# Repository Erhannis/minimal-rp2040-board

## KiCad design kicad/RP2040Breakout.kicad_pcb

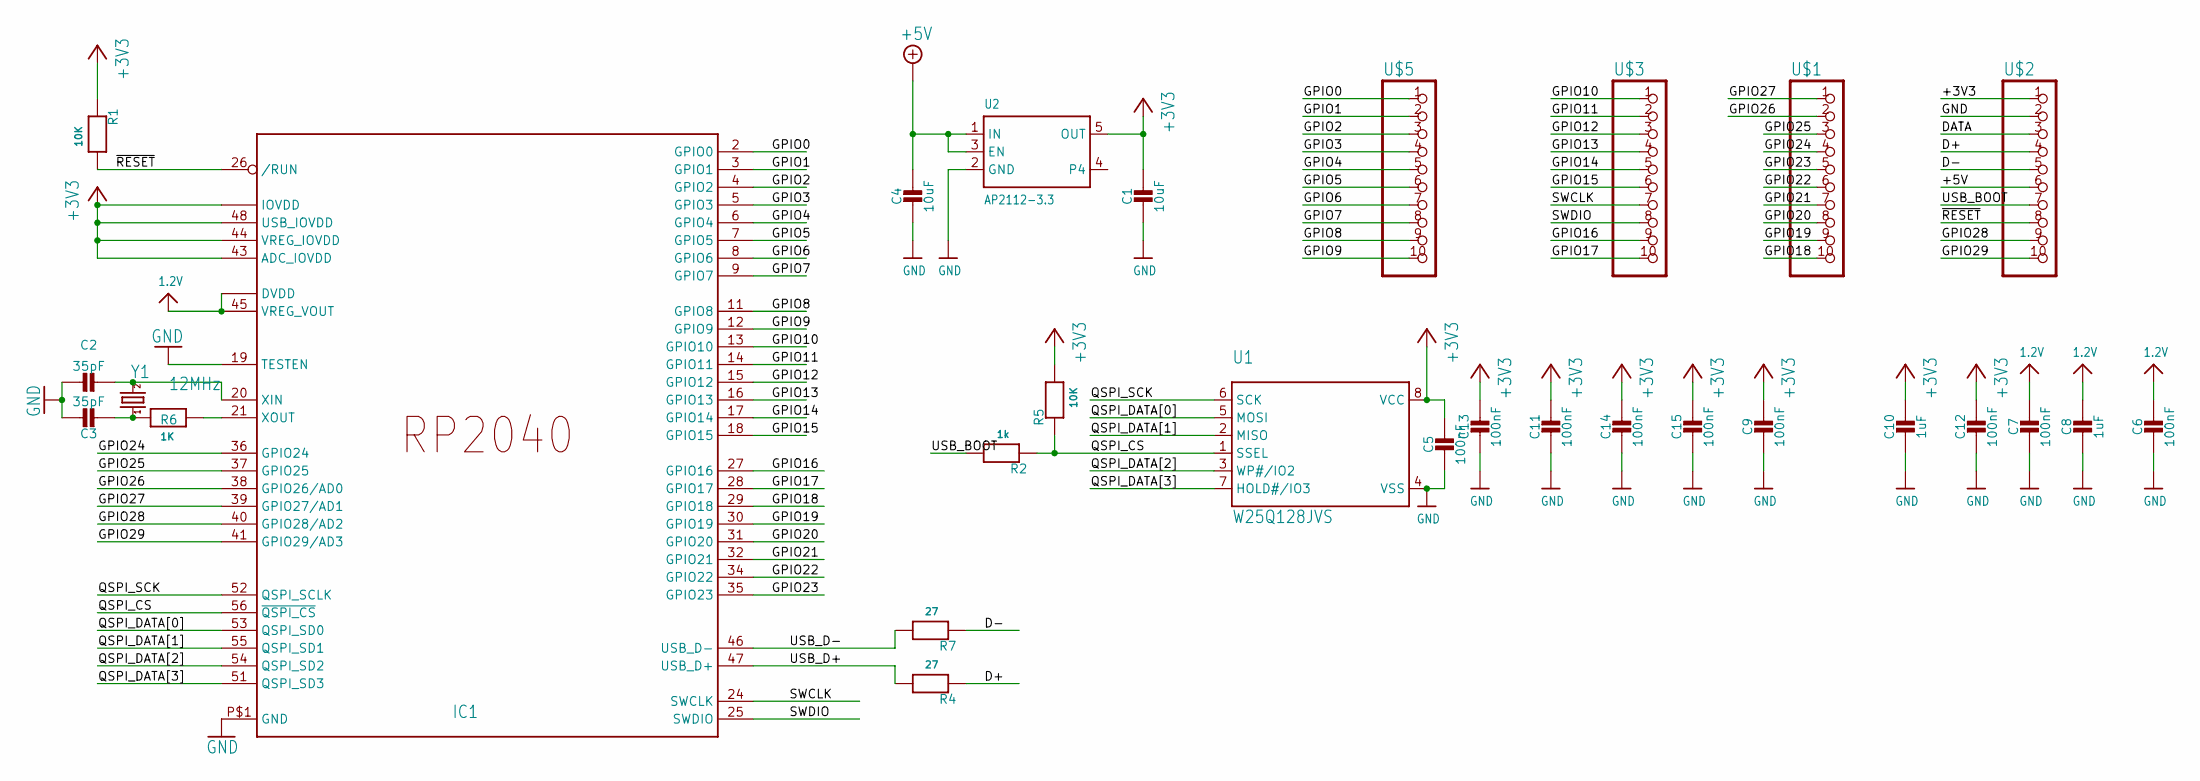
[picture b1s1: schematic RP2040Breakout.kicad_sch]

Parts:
C1, C4: 10uF; _0805MP; LCSC C1713
C2, C3: 35pF; _0402NO; LCSC C415391
C5, C6, C7, C9, C11, C12, C13, C14, C15: 100nF; _0402NO; LCSC C1525
C8, C10: 1uF; _0402NO; LCSC C14445
IC1: RP2040_QFN56; QFN56_7MM_REDUCEDEPAD; LCSC C2040
R1, R5: 10K; _0402NO; LCSC C60490
R2: 1k; _0402NO; LCSC C140196
R4, R7: 27; _0402NO; LCSC C25100
R6: 1K; _0402NO; LCSC C140196
U1: W25Q128JVS; SOIC8_208MIL; LCSC C97521
U2: AP2112-3.3; SOT23-5@1; LCSC C51118
U$1, U$2, U$3, U$5: HEADER-1X10ROUND; 1X10_ROUND
Y1: 12MHz; CRYSTAL-SMD-5X3; LCSC C362359

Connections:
1.2V: C6.1, C7.1, C8.1, IC1.23 (DVDD), IC1.45 (VREG_VOUT), IC1.50 (DVDD)
+3V3: C1.1, C5.1, C9.1, C10.1, C11.1, C12.1, C13.1, C14.1, C15.1, IC1.1 (IOVDD), IC1.10 (IOVDD), IC1.22 (IOVDD), IC1.33 (IOVDD), IC1.42 (IOVDD), IC1.43 (ADC_IOVDD), IC1.44 (VREG_IOVDD), IC1.48 (USB_IOVDD), IC1.49 (IOVDD), R1.1, R5.2, U1.8 (VCC), U2.5 (OUT), U$2.1
+5V: C4.1, U2.1 (IN), U2.3 (EN), U$2.6
/D+: R4.1, U$2.4
/D-: R7.1, U$2.5
/DATA: U$2.3
/GPIO0: IC1.2 (GPIO0), U$5.1
/GPIO1: IC1.3 (GPIO1), U$5.2
/GPIO2: IC1.4 (GPIO2), U$5.3
/GPIO3: IC1.5 (GPIO3), U$5.4
/GPIO4: IC1.6 (GPIO4), U$5.5
/GPIO5: IC1.7 (GPIO5), U$5.6
/GPIO6: IC1.8 (GPIO6), U$5.7
/GPIO7: IC1.9 (GPIO7), U$5.8
/GPIO8: IC1.11 (GPIO8), U$5.9
/GPIO9: IC1.12 (GPIO9), U$5.10
/GPIO10: IC1.13 (GPIO10), U$3.1
/GPIO11: IC1.14 (GPIO11), U$3.2
/GPIO12: IC1.15 (GPIO12), U$3.3
/GPIO13: IC1.16 (GPIO13), U$3.4
/GPIO14: IC1.17 (GPIO14), U$3.5
/GPIO15: IC1.18 (GPIO15), U$3.6
/GPIO16: IC1.27 (GPIO16), U$3.9
/GPIO17: IC1.28 (GPIO17), U$3.10
/GPIO18: IC1.29 (GPIO18), U$1.10
/GPIO19: IC1.30 (GPIO19), U$1.9
/GPIO20: IC1.31 (GPIO20), U$1.8
/GPIO21: IC1.32 (GPIO21), U$1.7
/GPIO22: IC1.34 (GPIO22), U$1.6
/GPIO23: IC1.35 (GPIO23), U$1.5
/GPIO24: IC1.36 (GPIO24), U$1.4
/GPIO25: IC1.37 (GPIO25), U$1.3
/GPIO26: IC1.38 (GPIO26/AD0), U$1.2
/GPIO27: IC1.39 (GPIO27/AD1), U$1.1
/GPIO28: IC1.40 (GPIO28/AD2), U$2.9
/GPIO29: IC1.41 (GPIO29/AD3), U$2.10
/QSPI_CS: IC1.56 (~QSPI_CS), R2.1, R5.1, U1.1 (SSEL)
/QSPI_DATA[0]: IC1.53 (QSPI_SD0), U1.5 (MOSI)
/QSPI_DATA[1]: IC1.55 (QSPI_SD1), U1.2 (MISO)
/QSPI_DATA[2]: IC1.54 (QSPI_SD2), U1.3 (WP#/IO2)
/QSPI_DATA[3]: IC1.51 (QSPI_SD3), U1.7 (HOLD#/IO3)
/QSPI_SCK: IC1.52 (QSPI_SCLK), U1.6 (SCK)
/SWCLK: IC1.24 (SWCLK), U$3.7
/SWDIO: IC1.25 (SWDIO), U$3.8
/USB_BOOT: R2.2, U$2.7
/USB_D+: IC1.47 (USB_D+), R4.2
/USB_D-: IC1.46 (USB_D-), R7.2
/~RESET: IC1.26 (/RUN), R1.2, U$2.8
GND: C1.2, C2.1, C3.1, C4.2, C5.2, C6.2, C7.2, C8.2, C9.2, C10.2, C11.2, C12.2, C13.2, C14.2, C15.2, IC1.19 (TESTEN), IC1.P$1 (GND), U1.4 (VSS), U2.2 (GND), U$2.2
unnamed: C3.2, R6.1, Y1.1
unnamed: C2.2, IC1.20 (XIN), Y1.3 (2)
unnamed: IC1.21 (XOUT), R6.2

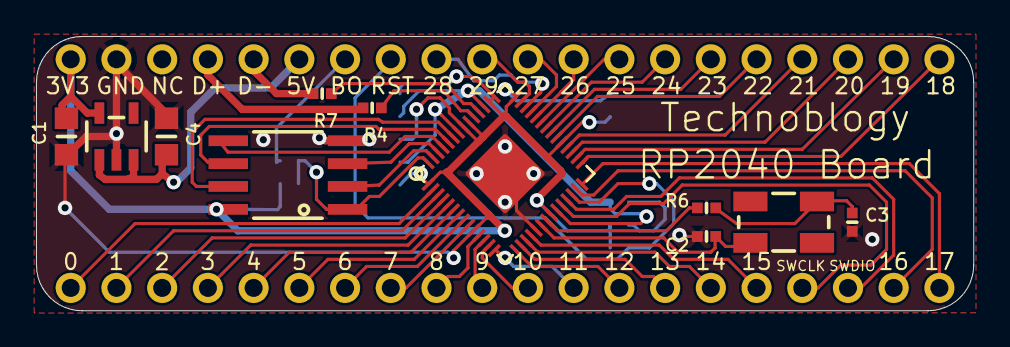
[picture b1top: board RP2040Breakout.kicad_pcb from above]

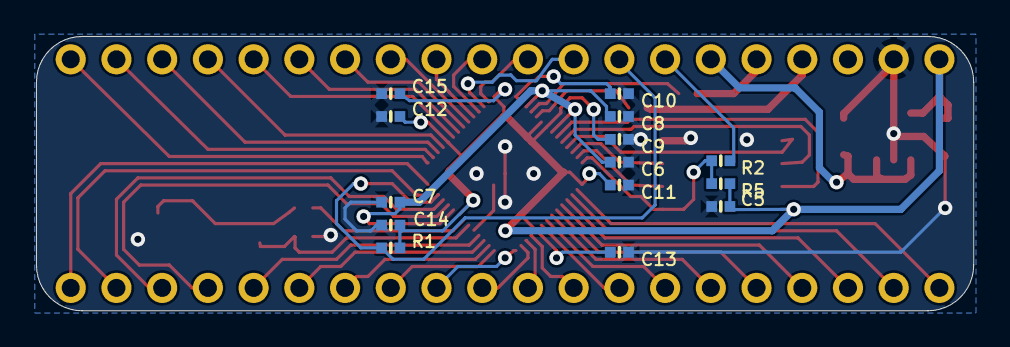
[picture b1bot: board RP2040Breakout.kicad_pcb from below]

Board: 2 copper layers, 52.1 x 15.2 mm, 29 parts (14 on the bottom side), 51 nets.

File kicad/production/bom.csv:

Designator,Footprint,Quantity,Value,LCSC Part #
"C1, C4",_0805MP,2,10uF,C1713
"C10, C8",_0402NO,2,1uF,C14445
"C11, C12, C13, C14, C15, C5, C6, C7, C9",_0402NO,9,100nF,C1525
"C2, C3",_0402NO,2,12pF,C326662
IC1,QFN56_7MM_REDUCEDEPAD,1,RP2040_QFN56,C2040
"R1, R5",_0402NO,2,10K,C60490
"R2, R6",_0402NO,2,1k,C140196
"R4, R7",_0402NO,2,27,C25100
"U$1, U$2, U$3, U$5",1X10_ROUND,4,HEADER-1X10ROUND,
U1,SOIC8_208MIL,1,W25Q128JVS,C97521
U2,SOT23-5@1,1,AP2112-3.3,C51118
Y1,CRYSTAL-SMD-5X3,1,12MHz,C362359

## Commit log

2023-08-07 Ok, I imported into kicad and also assigned JLCPCB part numbers
2023-08-07 Updated pcb footprints from schematic; fingers crossed
2023-08-07 Oh, zones, right
2023-08-07 Ok, I ordered some from JLCPCB, guess we'll see how it goes.
2023-08-07 There were 'unsaved changes' to the pcb, dunno what that's about
2023-08-14 Ooookay. So aside from the misunderstanding about capacitors, somehow the import process removed a single important trace. ...As far as I can tell. Namely, the GND connection for the voltage regulato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
